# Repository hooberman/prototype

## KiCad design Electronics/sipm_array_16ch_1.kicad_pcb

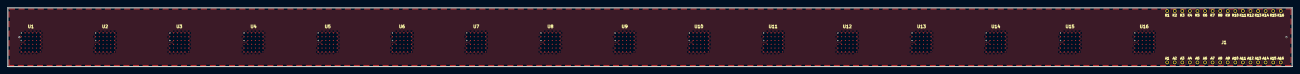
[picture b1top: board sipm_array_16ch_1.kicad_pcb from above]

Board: 4 copper layers, 339.1 x 15.5 mm, 17 parts (0 on the bottom side), 33 nets.

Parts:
J1: (no value)
U1, U2, U3, U4, U5, U6, U7, U8, U9, U10, U11, U12, U13, U14, U15, U16: (no value)

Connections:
Anode1: J1.A1, U1.C1, U1.D1
Anode2: J1.A2, U2.C1, U2.D1
Anode3: J1.A3, U3.C1, U3.D1
Anode4: J1.A4, U4.C1, U4.D1
Anode5: J1.A5, U5.C1, U5.D1
Anode6: J1.A6, U6.C1, U6.D1
Anode7: J1.A7, U7.C1, U7.D1
Anode8: J1.A8, U8.C1, U8.D1
Anode9: J1.A9, U9.C1, U9.D1
Anode10: J1.A10, U10.C1, U10.D1
Anode11: J1.A11, U11.C1, U11.D1
Anode12: J1.A12, U12.C1, U12.D1
Anode13: J1.A13, U13.C1, U13.D1
Anode14: J1.A14, U14.C1, U14.D1
Anode15: J1.A15, U15.C1, U15.D1
Anode16: J1.A16, U16.C1, U16.D1
Cathode1: J1.K1, U1.A1, U1.F6
Cathode2: J1.K2, U2.A1, U2.F6
Cathode3: J1.K3, U3.A1, U3.F6
Cathode4: J1.K4, U4.A1, U4.F6
Cathode5: J1.K5, U5.A1, U5.F6
Cathode6: J1.K6, U6.A1, U6.F6
Cathode7: J1.K7, U7.A1, U7.F6
Cathode8: J1.K8, U8.A1, U8.F6
Cathode9: J1.K9, U9.A1, U9.F6
Cathode10: J1.K10, U10.A1, U10.F6
Cathode11: J1.K11, U11.A1, U11.F6
Cathode12: J1.K12, U12.A1, U12.F6
Cathode13: J1.K13, U13.A1, U13.F6
Cathode14: J1.K14, U14.A1, U14.F6
Cathode15: J1.K15, U15.A1, U15.F6
Cathode16: J1.K16, U16.A1, U16.F6
GND: U1.A2, U1.A3, U1.A4, U1.A5, U1.A6, U1.B1, U1.B2, U1.B3, U1.B4, U1.B5, U1.B6, U1.C2, U1.C3, U1.C4, U1.C5, U1.C6, U1.D2, U1.D3, U1.D4, U1.D5, U1.D6, U1.E1, U1.E2, U1.E3, U1.E4, U1.E5, U1.E6, U1.F1, U1.F2, U1.F3, U1.F4, U1.F5, U2.A2, U2.A3, U2.A4, U2.A5, U2.A6, U2.B1, U2.B2, U2.B3, U2.B4, U2.B5, U2.B6, U2.C2, U2.C3, U2.C4, U2.C5, U2.C6, U2.D2, U2.D3, U2.D4, U2.D5, U2.D6, U2.E1, U2.E2, U2.E3, U2.E4, U2.E5, U2.E6, U2.F1, U2.F2, U2.F3, U2.F4, U2.F5, U3.A2, U3.A3, U3.A4, U3.A5, U3.A6, U3.B1, U3.B2, U3.B3, U3.B4, U3.B5, U3.B6, U3.C2, U3.C3, U3.C4, U3.C5, U3.C6, U3.D2, U3.D3, U3.D4, U3.D5, U3.D6, U3.E1, U3.E2, U3.E3, U3.E4, U3.E5, U3.E6, U3.F1, U3.F2, U3.F3, U3.F4, U3.F5, U4.A2, U4.A3, U4.A4, U4.A5, U4.A6, U4.B1, U4.B2, U4.B3, U4.B4, U4.B5, U4.B6, U4.C2, U4.C3, U4.C4, U4.C5, U4.C6, U4.D2, U4.D3, U4.D4, U4.D5, U4.D6, U4.E1, U4.E2, U4.E3, U4.E4, U4.E5, U4.E6, U4.F1, U4.F2, U4.F3, U4.F4, U4.F5, U5.A2, U5.A3, U5.A4, U5.A5, U5.A6, U5.B1, U5.B2, U5.B3, U5.B4, U5.B5, U5.B6, U5.C2, U5.C3, U5.C4, U5.C5, U5.C6, U5.D2, U5.D3, U5.D4, U5.D5, U5.D6, U5.E1, U5.E2, U5.E3, U5.E4, U5.E5, U5.E6, U5.F1, U5.F2, U5.F3, U5.F4, U5.F5, U6.A2, U6.A3, U6.A4, U6.A5, U6.A6, U6.B1, U6.B2, U6.B3, U6.B4, U6.B5, U6.B6, U6.C2, U6.C3, U6.C4, U6.C5, U6.C6, U6.D2, U6.D3, U6.D4, U6.D5, U6.D6, U6.E1, U6.E2, U6.E3, U6.E4, U6.E5, U6.E6, U6.F1, U6.F2, U6.F3, U6.F4, U6.F5, U7.A2, U7.A3, U7.A4, U7.A5, U7.A6, U7.B1, U7.B2, U7.B3, U7.B4, U7.B5, U7.B6, U7.C2, U7.C3, U7.C4, U7.C5, U7.C6, U7.D2, U7.D3, U7.D4, U7.D5, U7.D6, U7.E1, U7.E2, U7.E3, U7.E4, U7.E5, U7.E6, U7.F1, U7.F2, U7.F3, U7.F4, U7.F5, U8.A2, U8.A3, U8.A4, U8.A5, U8.A6, U8.B1, U8.B2, U8.B3, U8.B4, U8.B5, U8.B6, U8.C2, U8.C3, U8.C4, U8.C5, U8.C6, U8.D2, U8.D3, U8.D4, U8.D5, U8.D6, U8.E1, U8.E2, U8.E3, U8.E4, U8.E5, U8.E6, U8.F1, U8.F2, U8.F3, U8.F4, U8.F5, U9.A2, U9.A3, U9.A4, U9.A5, U9.A6, U9.B1, U9.B2, U9.B3, U9.B4, U9.B5, U9.B6, U9.C2, U9.C3, U9.C4, U9.C5, U9.C6, U9.D2, U9.D3, U9.D4, U9.D5, U9.D6, U9.E1, U9.E2, U9.E3, U9.E4, U9.E5, U9.E6, U9.F1, U9.F2, U9.F3, U9.F4, U9.F5, U10.A2, U10.A3, U10.A4, U10.A5, U10.A6, U10.B1, U10.B2, U10.B3, U10.B4, U10.B5, U10.B6, U10.C2, U10.C3, U10.C4, U10.C5, U10.C6, U10.D2, U10.D3, U10.D4, U10.D5, U10.D6, U10.E1, U10.E2, U10.E3, U10.E4, U10.E5, U10.E6, U10.F1, U10.F2, U10.F3, U10.F4, U10.F5, U11.A2, U11.A3, U11.A4, U11.A5, U11.A6, U11.B1, U11.B2, U11.B3, U11.B4, U11.B5, U11.B6, U11.C2, U11.C3, U11.C4, U11.C5, U11.C6, U11.D2, U11.D3, U11.D4, U11.D5, U11.D6, U11.E1, U11.E2, U11.E3, U11.E4, U11.E5, U11.E6, U11.F1, U11.F2, U11.F3, U11.F4, U11.F5, U12.A2, U12.A3, U12.A4, U12.A5, U12.A6, U12.B1, U12.B2, U12.B3, U12.B4, U12.B5, U12.B6, U12.C2, U12.C3, U12.C4, U12.C5, U12.C6, U12.D2, U12.D3, U12.D4, U12.D5, U12.D6, U12.E1, U12.E2, U12.E3, U12.E4, U12.E5, U12.E6, U12.F1, U12.F2, U12.F3, U12.F4, U12.F5, U13.A2, U13.A3, U13.A4, U13.A5, U13.A6, U13.B1, U13.B2, U13.B3, U13.B4, U13.B5, U13.B6, U13.C2, U13.C3, U13.C4, U13.C5, U13.C6, U13.D2, U13.D3, U13.D4, U13.D5, U13.D6, U13.E1, U13.E2, U13.E3, U13.E4, U13.E5, U13.E6, U13.F1, U13.F2, U13.F3, U13.F4, U13.F5, U14.A2, U14.A3, U14.A4, U14.A5, U14.A6, U14.B1, U14.B2, U14.B3, U14.B4, U14.B5, U14.B6, U14.C2, U14.C3, U14.C4, U14.C5, U14.C6, U14.D2, U14.D3, U14.D4, U14.D5, U14.D6, U14.E1, U14.E2, U14.E3, U14.E4, U14.E5, U14.E6, U14.F1, U14.F2, U14.F3, U14.F4, U14.F5, U15.A2, U15.A3, U15.A4, U15.A5, U15.A6, U15.B1, U15.B2, U15.B3, U15.B4, U15.B5, U15.B6, U15.C2, U15.C3, U15.C4, U15.C5, U15.C6, U15.D2, U15.D3, U15.D4, U15.D5, U15.D6, U15.E1, U15.E2, U15.E3, U15.E4, U15.E5, U15.E6, U15.F1, U15.F2, U15.F3, U15.F4, U15.F5, U16.A2, U16.A3, U16.A4, U16.A5, U16.A6, U16.B1, U16.B2, U16.B3, U16.B4, U16.B5, U16.B6, U16.C2, U16.C3, U16.C4, U16.C5, U16.C6, U16.D2, U16.D3, U16.D4, U16.D5, U16.D6, U16.E1, U16.E2, U16.E3, U16.E4, U16.E5, U16.E6, U16.F1, U16.F2, U16.F3, U16.F4, U16.F5
